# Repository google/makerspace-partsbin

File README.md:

# Makerspace Partsbin

This repository houses various things (3D models, circuits, class materials)
that we've created for use in Google makerspaces.

If you'd like to contribute, see [CONTRIBUTING](CONTRIBUTING.md)

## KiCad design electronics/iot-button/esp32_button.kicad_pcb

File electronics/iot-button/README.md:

# IoT Button

This is a single-button (with some IOs broken out) that can use deep sleep or
fully turn off in between uses.

Stack-up, inside a 3d printed case...

    Button Cap
    Board (0.8mm)
    Small LiPO

Results in a pretty small overall package that's not quite pocket-sized.

## Build

The build by hand will probably require a microscope (for Q301, part of the
auto-reset circuit) and a very good soldering iron (exposed pads, although there
vias so you can head from the other side).

The USB connector is one that doesn't require slots for mounting, so this board
can be made at osh park.

## Verification

The power-off functionality works, on wakeup you need to assert IO12 as long as
you want to stay powered-up.  The U402 (single pixel) works, although it draws a
*lot* from the 3v3 rail.  The IO4 voltage measurement is expected to only work
as a rough measurement, given results on previous similar circuits.

## USB Power

The overall power budget is an estimate that hasn't been verified yet.  Maximum
stable draw is with an exhausted LiPO + busy ESP32, and the draw at the USB
port shouldn't exceed 500mA.

Capacitance has been minimized that would affect inrush current, and previous
prototypes with similar circuits were acceptable, but this should be measured.

## Known Issues

* v0.3
  * some broken-out IOs are unusable
  * regulator part number is incorrect; it needs one with higher current
  * CH340 variant can't program faster than 115k (perhaps a limitation of the
    xtal-less one)
* v0.2
  * url is wrong, U402 rotated 180

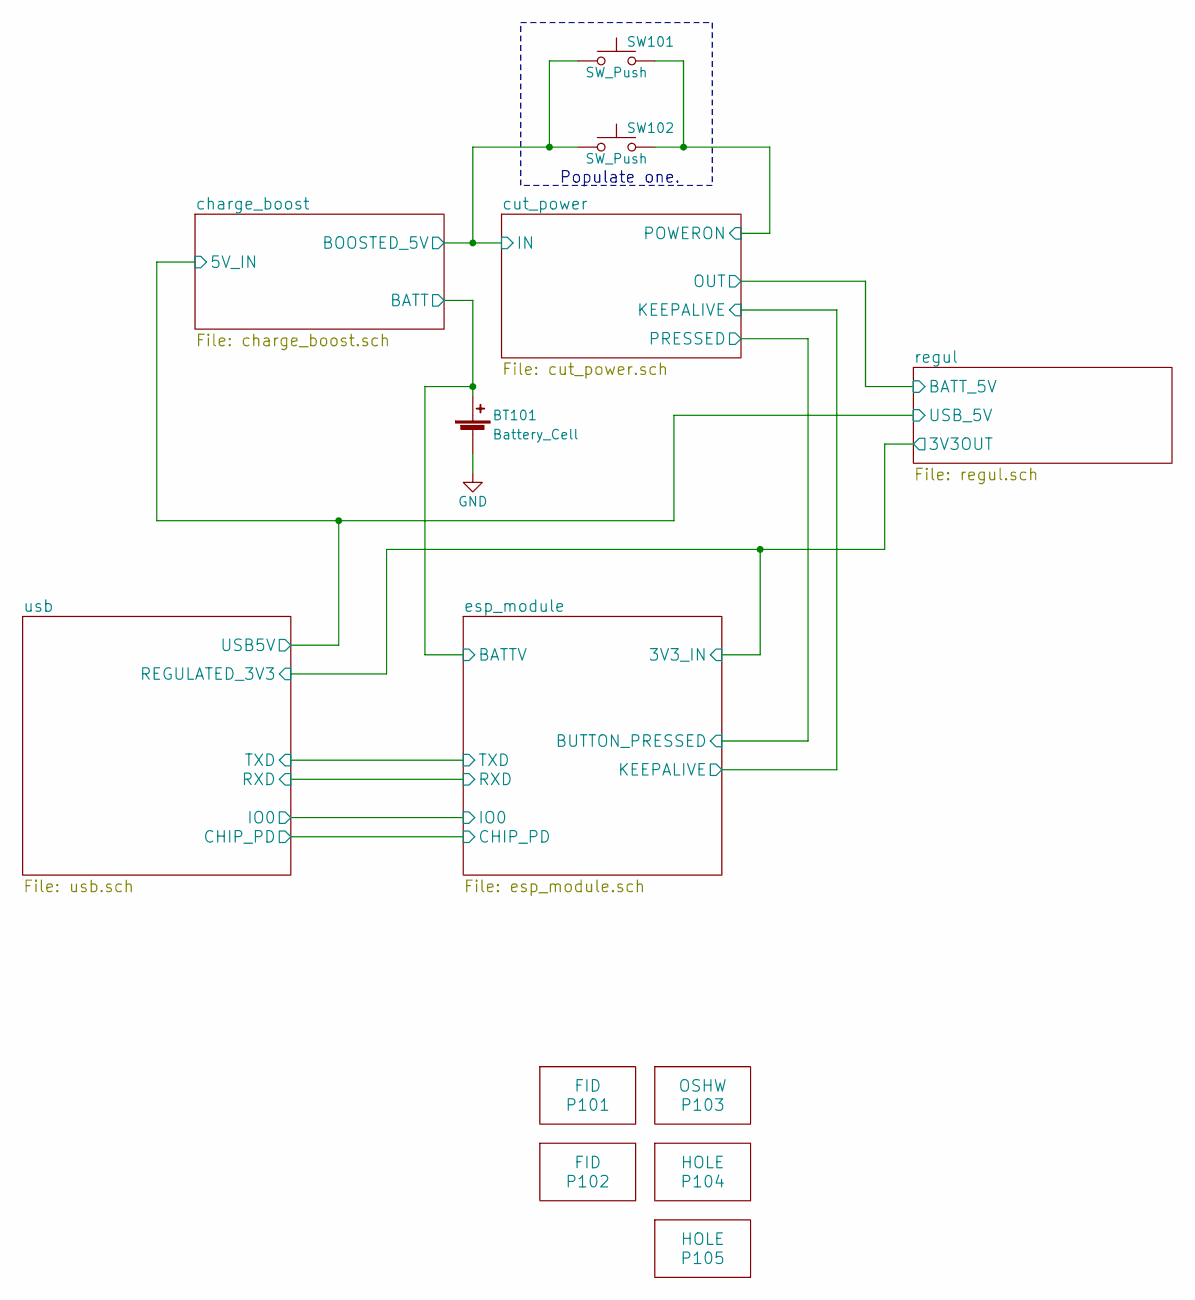
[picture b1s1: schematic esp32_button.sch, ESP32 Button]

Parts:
BT101: Battery_Cell; JST_PH_2_Combo; MPN S2B-PH-K-S(LF)(SN)
P101, P102: FID; Fiducial_1mm_Dia_2.54mm_Outer_CopperTop
P103: OSHW; OSHW-Symbol_8.9x8mm_SilkScreen
P104, P105: HOLE; MountingHole_3mm
SW101: SW_Push; SW_SPST_EVQP0
SW102: SW_Push; SW_SPST_PTS645; MPN? PTS525SM15SMTR2 LFS

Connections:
/charge_boost/BATT: BT101.1 (+); also elsewhere on the board
/charge_boost/BOOSTED_5V: SW101.1, SW102.1; also elsewhere on the board
/cut_power/POWERON: SW101.2, SW102.2; also elsewhere on the board
GND: BT101.2 (-); also elsewhere on the board

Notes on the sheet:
Populate one.

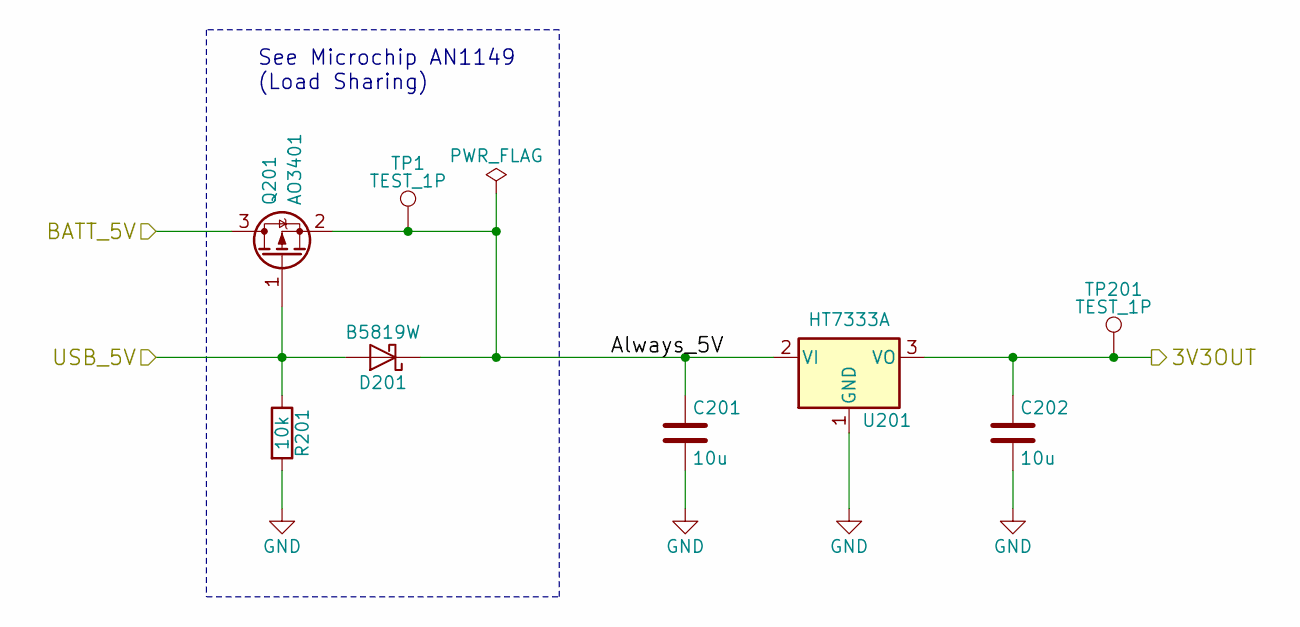
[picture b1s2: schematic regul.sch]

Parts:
C201, C202: 10u; C_0805
D201: B5819W; D_SOD-123; MPN B5819WS-TP
Q201: AO3401; SOT-23
R201: 10k; R_0603_HandSoldering
TP1, TP201: TEST_1P; Test_Point_SMD
U201: HT7333A; SOT-89-3

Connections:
/charge_boost/5V_IN: D201.2 (A), Q201.1 (G), R201.1; also elsewhere on the board
/regul/3V3OUT: C202.1, TP201.1, U201.3 (VO); also elsewhere on the board
/regul/Always_5V: C201.1, D201.1 (K), Q201.2 (S), TP1.1, U201.2 (VI)
/regul/BATT_5V: Q201.3 (D); also elsewhere on the board
GND: C201.2, C202.2, R201.2, U201.1 (GND); also elsewhere on the board

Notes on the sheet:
See Microchip AN1149 (Load Sharing)

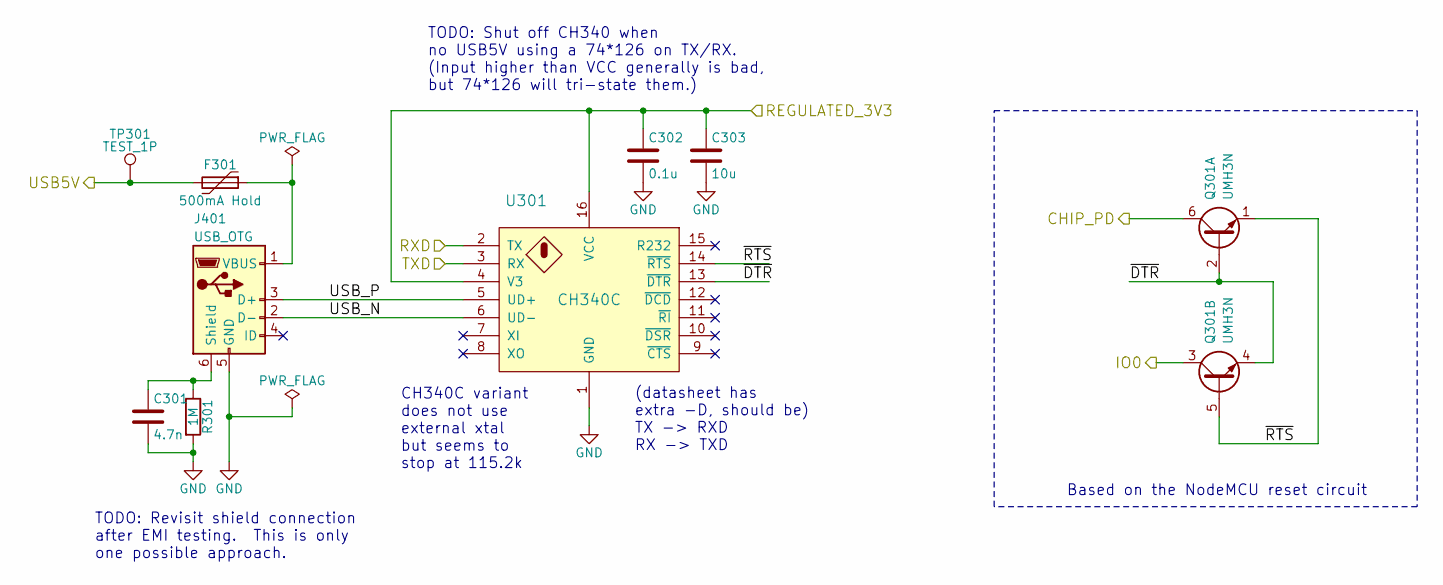
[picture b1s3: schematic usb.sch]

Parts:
C301: 4.7n; C_0603; MPN GRM188R71H472KA01D
C302: 0.1u; C_0603
C303: 10u; C_0805; MPN C0805C106K8PACTU
F301: 500mA Hold; Fuse_SMD1206_HandSoldering; MPN 0ZCJ0050FF2G
J401: USB_OTG; USB_Micro-B_Amphenol-10118194-0001LF_CircularHoles; MPN 10118194-0001LF
Q301: UMH3N; SOT-363_SC-70-6_Handsoldering
R301: 1M; R_0603_HandSoldering
TP301: TEST_1P; Test_Point_SMD
U401: CH340C; SOIC-16_3.9x9.9mm_Pitch1.27mm

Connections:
/charge_boost/5V_IN: F301.2, TP301.1; also elsewhere on the board
/esp_module/CHIP_PD: Q301.6 (C1); also elsewhere on the board
/esp_module/IO0: Q301.3 (C2); also elsewhere on the board
/regul/3V3OUT: C302.1, C303.1; also elsewhere on the board
/usb/USB_N: J401.2 (D-); also elsewhere on the board
/usb/USB_P: J401.3 (D+); also elsewhere on the board
/usb/~DTR: Q301.2 (B1), Q301.4 (E2); also elsewhere on the board
/usb/~RTS: Q301.1 (E1), Q301.5 (B2); also elsewhere on the board
GND: C301.2, C302.2, C303.2, J401.5 (GND), R301.2; also elsewhere on the board
unnamed: C301.1, J401.6 (Shield), R301.1
unnamed: F301.1, J401.1 (VBUS)

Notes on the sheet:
Based on the NodeMCU reset circuit
CH340C variant does not use external xtal but seems to stop at 115.2k
TODO: Shut off CH340 when no USB5V using a 74*126 on TX/RX. (Input higher than VCC generally is bad, but 74*126 will tri-state them.)
TODO: Revisit shield connection after EMI testing. This is only one possible approach.
(datasheet has extra -D, should be) TX -> RXD RX -> TXD

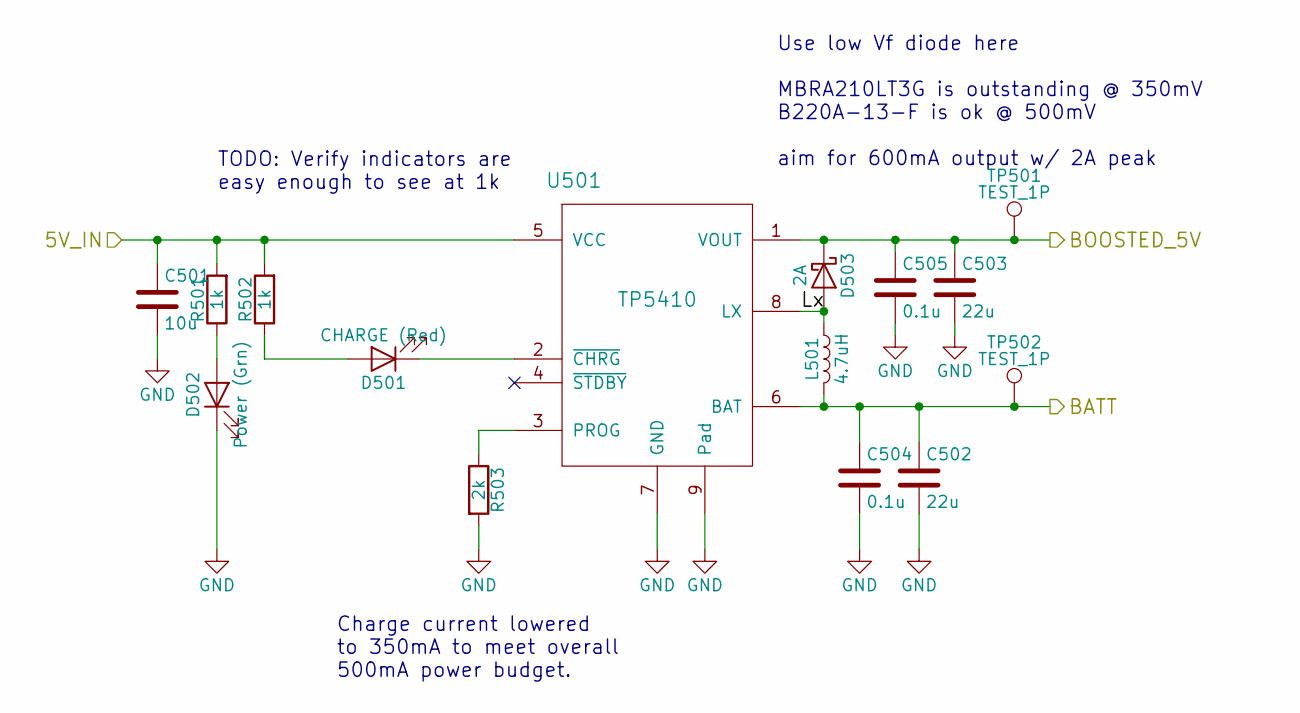
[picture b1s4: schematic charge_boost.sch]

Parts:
C501: 10u; C_0805
C502, C503: 22u; C_0805; MPN C0805C226M8PAC7800
C504: 0.1u; C_0603
C505: 0.1u; C_0603; MPN GRM033R61A104KE15D
D501: CHARGE (Red); LED_0603; MPN SML-D12V8WT86
D502: Power (Grn); LED_0603; MPN SML-D13M8WT86
D503: 2A; D_SMB; MPN MBRA210LT3G
L501: 4.7uH; Inductor_Taiyo-Yuden_NR-40xx_HandSoldering; MPN ASPI-4030S-4R7M-T
R501, R502: 1k; R_0402
R503: 2k; R_0603_HandSoldering
TP501, TP502: TEST_1P; Test_Point_SMD
U501: TP5410; SOIC-8-1EP_3.9x4.9mm_Pitch1.27mm

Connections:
/charge_boost/5V_IN: C501.1, R501.2, R502.2, U501.5 (VCC); also elsewhere on the board
/charge_boost/BATT: C502.1, C504.1, L501.2, TP502.1, U501.6 (BAT); also elsewhere on the board
/charge_boost/BOOSTED_5V: C503.1, C505.1, D503.1 (K), TP501.1, U501.1 (VOUT); also elsewhere on the board
/charge_boost/Lx: D503.2 (A), L501.1, U501.8 (LX)
GND: C501.2, C502.2, C503.2, C504.2, C505.2, D502.1 (K), R503.2, U501.7 (GND), U501.9 (Pad); also elsewhere on the board
unnamed: D501.1 (K), U501.2 (~CHRG)
unnamed: D501.2 (A), R502.1
unnamed: D502.2 (A), R501.1
unnamed: R503.1, U501.3 (PROG)

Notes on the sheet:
Charge current lowered to 350mA to meet overall 500mA power budget.
Use low Vf diode here MBRA210LT3G is outstanding @ 350mV B220A-13-F is ok @ 500mV aim for 600mA output w/ 2A peak
TODO: Verify indicators are easy enough to see at 1k

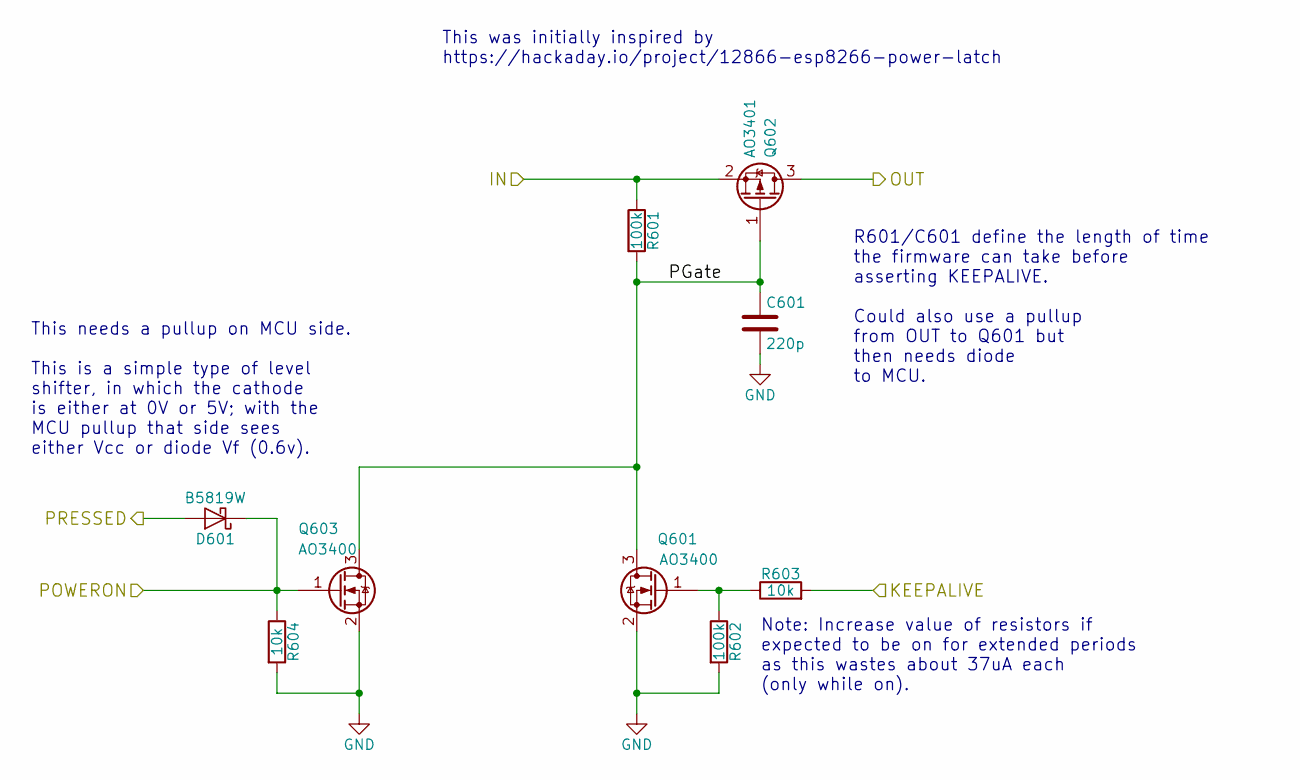
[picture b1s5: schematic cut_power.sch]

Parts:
C601: 220p; C_0603; MPN C1608X7R1C224K080AC
D601: B5819W; D_SOD-123; MPN B5819WS-TP
Q601, Q603: AO3400; SOT-23
Q602: AO3401; SOT-23
R601, R602: 100k; R_0603_HandSoldering
R603, R604: 10k; R_0603_HandSoldering

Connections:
/charge_boost/BOOSTED_5V: Q602.2 (S), R601.1; also elsewhere on the board
/cut_power/KEEPALIVE: R603.2; also elsewhere on the board
/cut_power/PGate: C601.1, Q601.3 (D), Q602.1 (G), Q603.3 (D), R601.2
/cut_power/POWERON: D601.1 (K), Q603.1 (G), R604.1; also elsewhere on the board
/esp_module/BUTTON_PRESSED: D601.2 (A); also elsewhere on the board
/regul/BATT_5V: Q602.3 (D); also elsewhere on the board
GND: C601.2, Q601.2 (S), Q603.2 (S), R602.2, R604.2; also elsewhere on the board
unnamed: Q601.1 (G), R602.1, R603.1

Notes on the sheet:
Note: Increase value of resistors if expected to be on for extended periods as this wastes about 37uA each (only while on).
R601/C601 define the length of time the firmware can take before asserting KEEPALIVE. Could also use a pullup from OUT to Q601 but then needs diode to MCU.
This was initially inspired by https://hackaday.io/project/12866-esp8266-power-latch
This needs a pullup on MCU side. This is a simple type of level shifter, in which the cathode is either at 0V or 5V; with the MCU pullup that side sees either Vcc or diode Vf (0.6v).

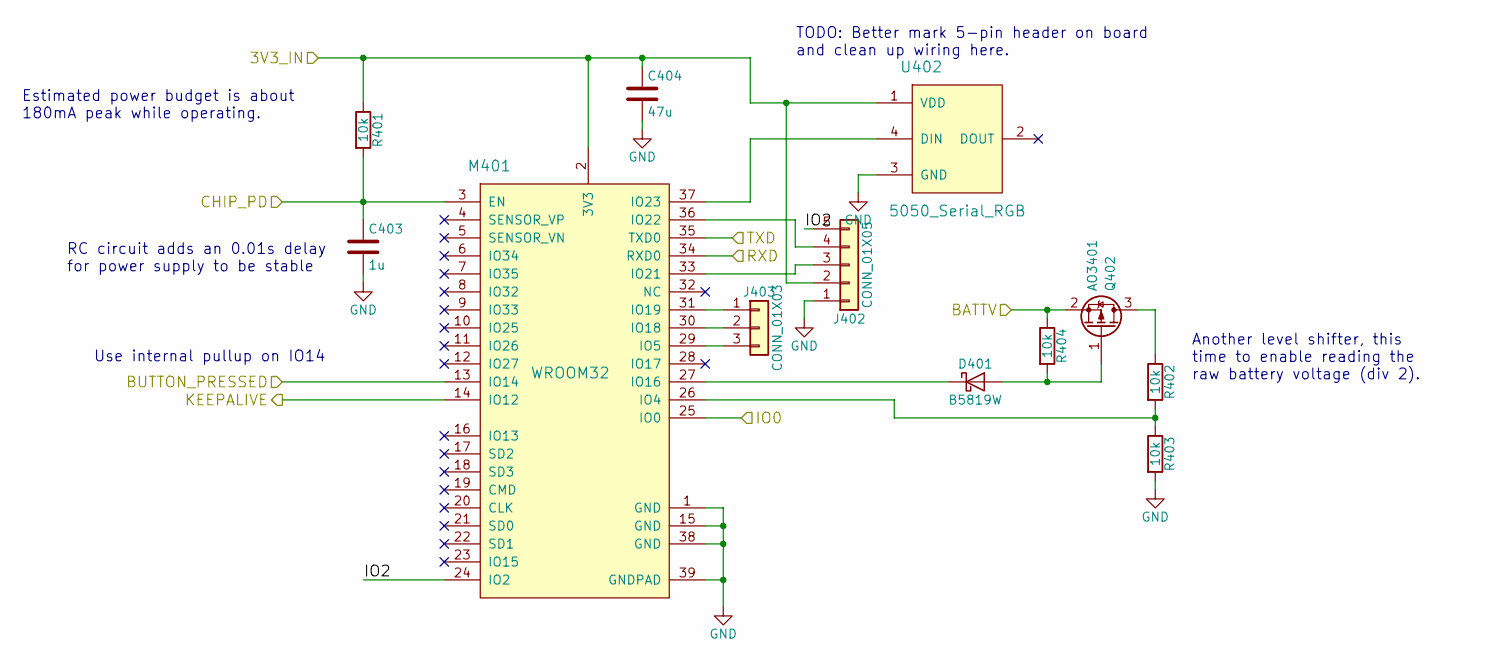
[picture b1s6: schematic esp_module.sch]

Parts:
C403: 1u; C_0805; MPN C0805C105K3PACTU
C404: 47u; C_1206; MPN C1206C476M9PACTU
D401: B5819W; D_SOD-123; MPN B5819WS-TP
J402: CONN_01X05; Pin_Header_Straight_1x05_Pitch2.54mm
J403: CONN_01X03; Pin_Header_Straight_1x03_Pitch2.54mm
M401: WROOM32
Q402: AO3401; SOT-23
R401, R402, R403, R404: 10k; R_0603_HandSoldering
U402: 5050_Serial_RGB; LED_WS2812B-PLCC4

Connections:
/charge_boost/BATT: Q402.2 (S), R404.1; also elsewhere on the board
/cut_power/KEEPALIVE: M401.14 (IO12); also elsewhere on the board
/esp_module/BUTTON_PRESSED: M401.13 (IO14); also elsewhere on the board
/esp_module/CHIP_PD: C403.1, M401.3 (EN), R401.2; also elsewhere on the board
/esp_module/IO0: M401.25 (IO0); also elsewhere on the board
/esp_module/IO2: J402.5, M401.24 (IO2)
/esp_module/RXD: M401.34 (RXD0); also elsewhere on the board
/esp_module/TXD: M401.35 (TXD0); also elsewhere on the board
/regul/3V3OUT: C404.1, J402.2, M401.2 (3V3), R401.1, U402.1 (VDD); also elsewhere on the board
GND: C403.2, C404.2, J402.1, M401.1 (GND), M401.15 (GND), M401.38 (GND), M401.39 (GNDPAD), R403.2, U402.3 (GND); also elsewhere on the board
unnamed: D401.1 (K), M401.27 (IO16)
unnamed: D401.2 (A), Q402.1 (G), R404.2
unnamed: J402.3, M401.33 (IO21)
unnamed: J402.4, M401.36 (IO22)
unnamed: J403.1, M401.31 (IO19)
unnamed: J403.2, M401.30 (IO18)
unnamed: J403.3, M401.29 (IO5)
unnamed: M401.26 (IO4), R402.2, R403.1
unnamed: M401.37 (IO23), U402.4 (DIN)
unnamed: Q402.3 (D), R402.1

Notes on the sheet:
TODO: Better mark 5-pin header on board and clean up wiring here.
RC circuit adds an 0.01s delay for power supply to be stable
Use internal pullup on IO14
Estimated power budget is about 180mA peak while operating.
Another level shifter, this time to enable reading the raw battery voltage (div 2).

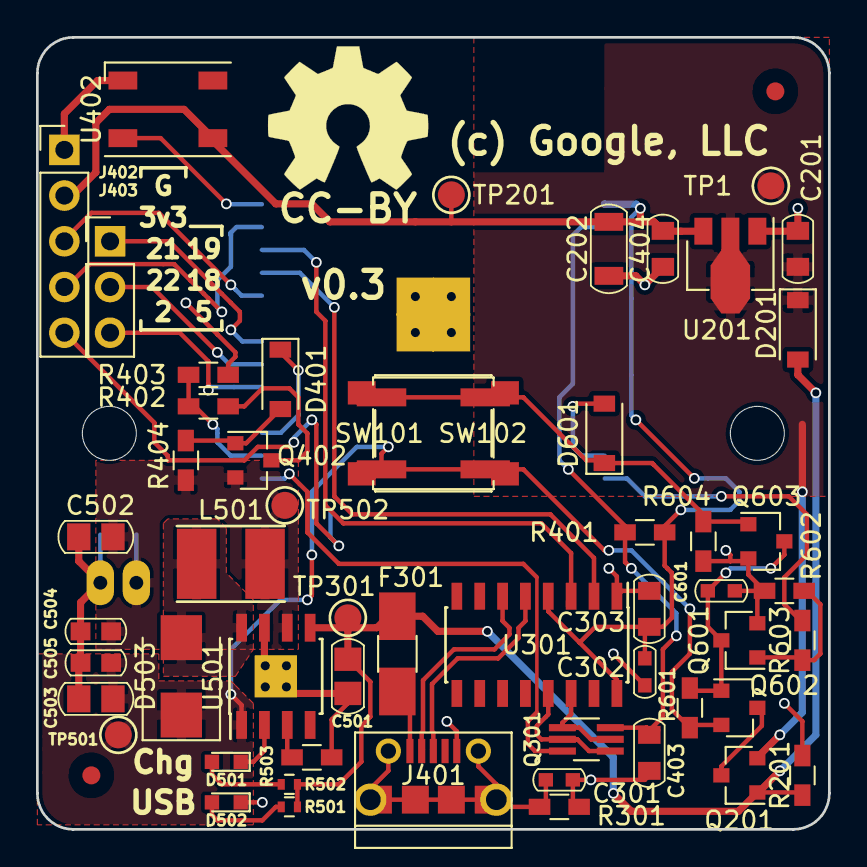
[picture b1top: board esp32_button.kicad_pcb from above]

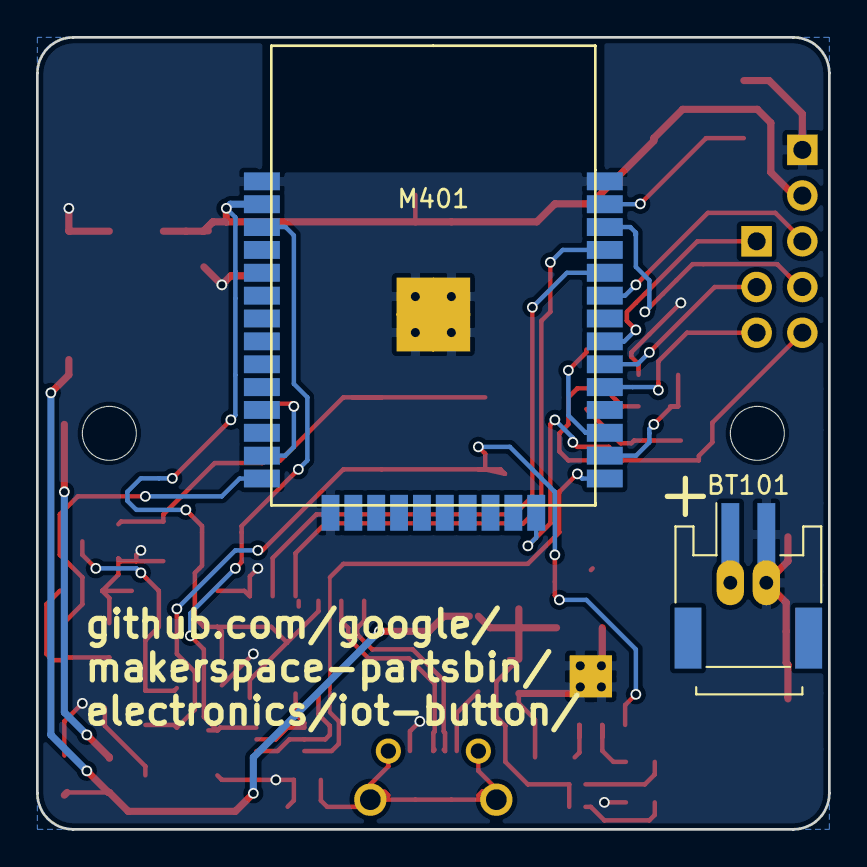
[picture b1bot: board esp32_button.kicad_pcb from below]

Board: 2 copper layers, 44.0 x 44.0 mm, 61 parts (2 on the bottom side), 38 nets.

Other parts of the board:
U301: CH340C; SOIC-16_3.9x9.9mm_Pitch1.27mm

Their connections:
/esp_module/RXD: U301.2; also elsewhere on the board
/esp_module/TXD: U301.3; also elsewhere on the board
/regul/3V3OUT: U301.4, U301.16; also elsewhere on the board
/usb/USB_N: U301.6; also elsewhere on the board
/usb/USB_P: U301.5; also elsewhere on the board
/usb/~DTR: U301.13; also elsewhere on the board
/usb/~RTS: U301.14; also elsewhere on the board
GND: U301.1; also elsewhere on the board

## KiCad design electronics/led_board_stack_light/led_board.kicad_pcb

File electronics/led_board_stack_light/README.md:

This is a work-in-progress to build a laser-cuttable stack light.  Best if the
soldermask is white.

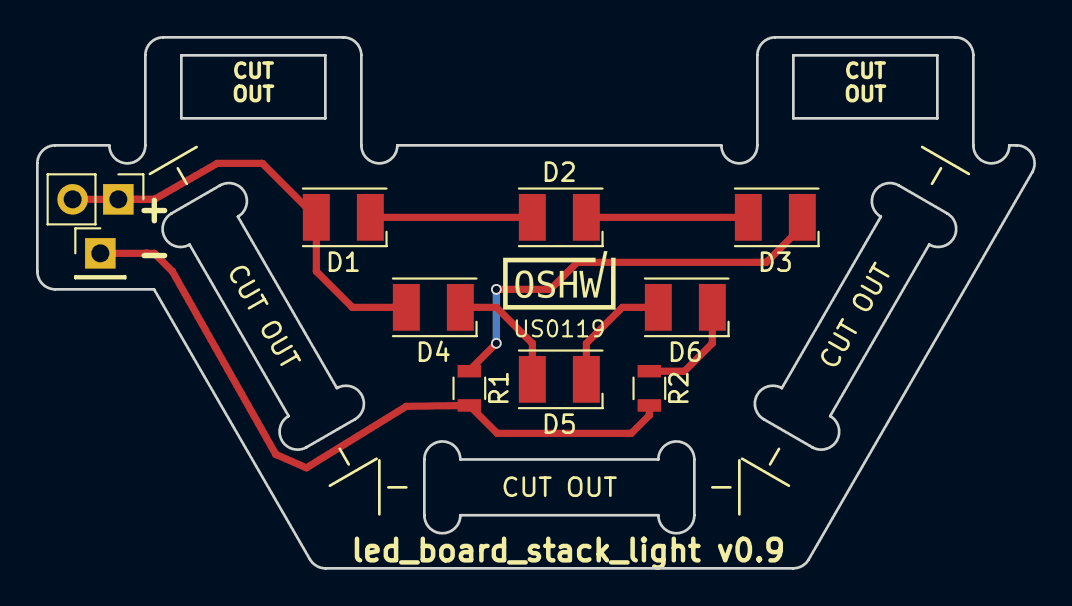
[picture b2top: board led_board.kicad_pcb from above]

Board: 2 copper layers, 55.4 x 29.5 mm, 15 parts (1 on the bottom side), 8 nets.

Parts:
D1, D2, D3, D4, D5, D6: LED; LED_PLCC-2
J1: CONN_01X02; Pin_Header_Straight_1x02_Pitch2.54mm
J2: CONN_01X01; Pin_Header_Straight_1x01_Pitch2.54mm
P1: OSHW; OSHW-Logo2_9.8x8mm_SilkScreen
P2, P3, P4: Slot; Slot_3.1x15
P5: US0119; OSHW_Mono_0.15_Scale
R1, R2: 56R; R_0805

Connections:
unnamed: D1.1, D2.2
unnamed: D1.2, D4.2, J1.1, J1.2
unnamed: D2.1, D3.2
unnamed: D3.1, R1.1
unnamed: D4.1, D5.2
unnamed: D5.1, D6.2
unnamed: D6.1, R2.1
unnamed: J2.1, R1.2, R2.2

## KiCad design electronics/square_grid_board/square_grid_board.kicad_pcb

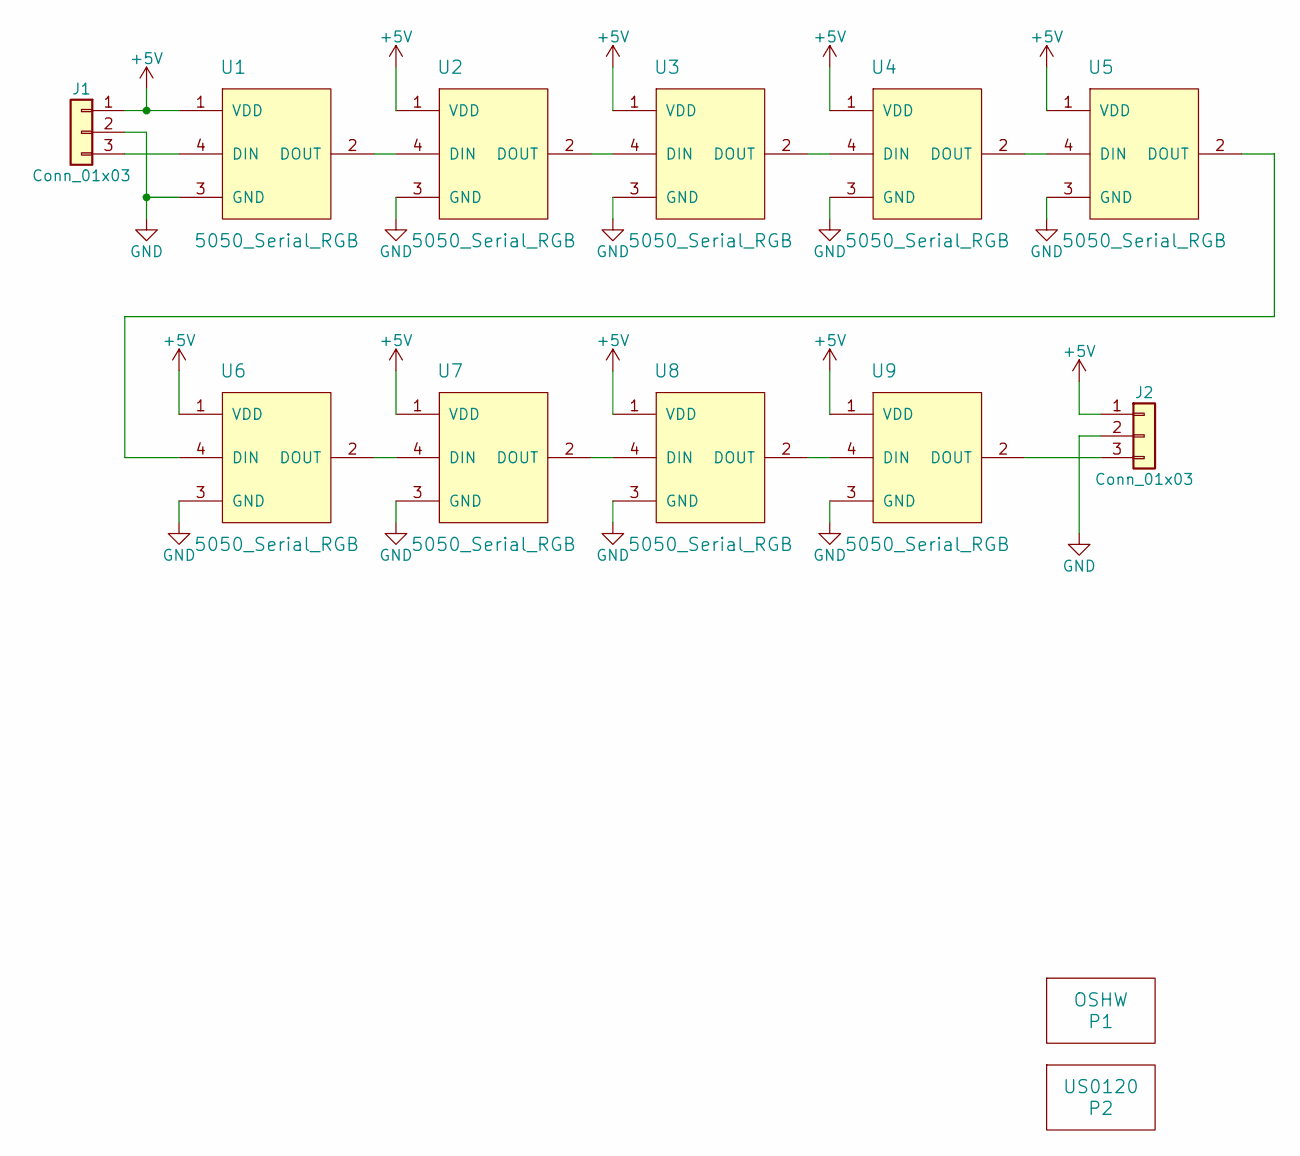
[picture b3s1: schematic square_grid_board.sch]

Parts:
J1, J2: Conn_01x03; JST_XH_S03B-XH-A_03x2.50mm_Angled
P1: OSHW; OSHW-Logo2_7.3x6mm_SilkScreen
P2: US0120; OSHW_Mono_0.20_Scale
U1, U2, U3, U4, U5, U6, U7, U8, U9: 5050_Serial_RGB; LED_WS2812B-PLCC4

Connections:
+5V: J1.1, J2.1, U1.1 (VDD), U2.1 (VDD), U3.1 (VDD), U4.1 (VDD), U5.1 (VDD), U6.1 (VDD), U7.1 (VDD), U8.1 (VDD), U9.1 (VDD)
GND: J1.2, J2.2, U1.3 (GND), U2.3 (GND), U3.3 (GND), U4.3 (GND), U5.3 (GND), U6.3 (GND), U7.3 (GND), U8.3 (GND), U9.3 (GND)
unnamed: J1.3, U1.4 (DIN)
unnamed: J2.3, U9.2 (DOUT)
unnamed: U1.2 (DOUT), U2.4 (DIN)
unnamed: U2.2 (DOUT), U3.4 (DIN)
unnamed: U3.2 (DOUT), U4.4 (DIN)
unnamed: U4.2 (DOUT), U5.4 (DIN)
unnamed: U5.2 (DOUT), U6.4 (DIN)
unnamed: U6.2 (DOUT), U7.4 (DIN)
unnamed: U7.2 (DOUT), U8.4 (DIN)
unnamed: U8.2 (DOUT), U9.4 (DIN)

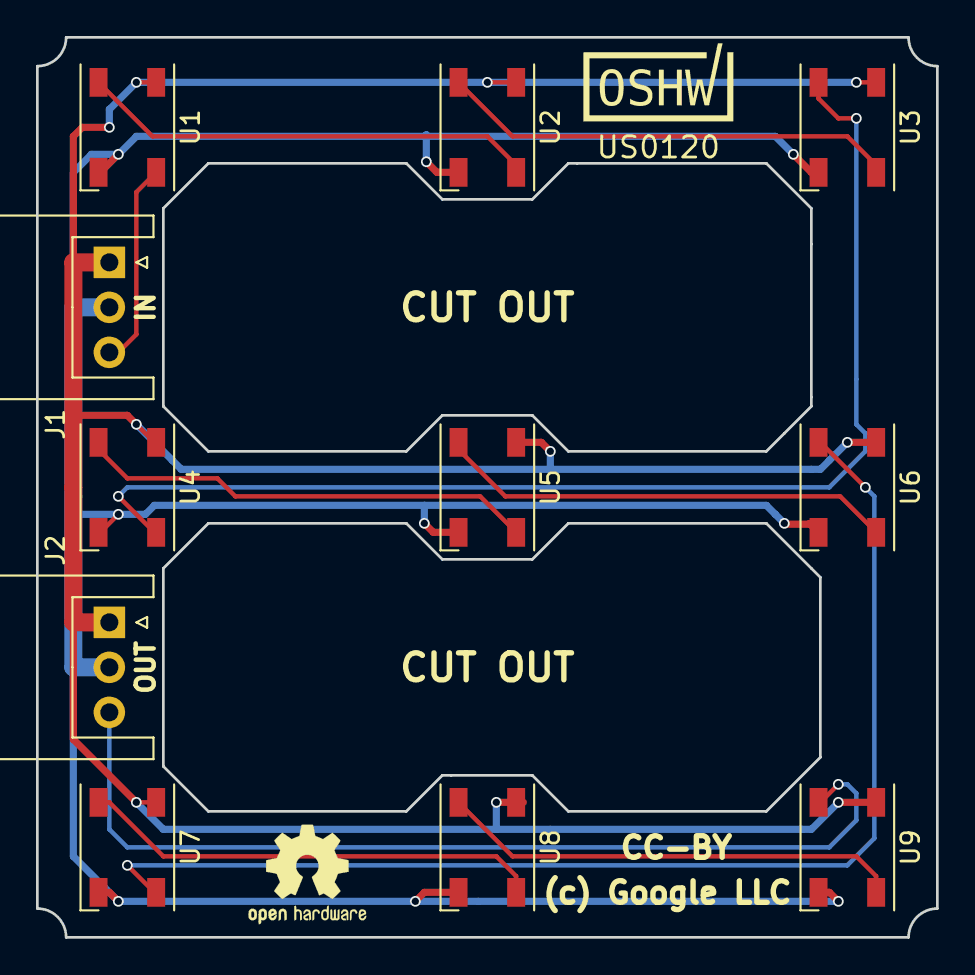
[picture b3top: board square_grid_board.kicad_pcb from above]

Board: 2 copper layers, 50.0 x 50.0 mm, 13 parts (0 on the bottom side), 12 nets.

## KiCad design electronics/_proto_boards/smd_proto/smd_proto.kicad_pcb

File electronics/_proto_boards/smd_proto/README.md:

This board is inspired by https://www.sparkfun.com/products/retired/8708 , https://hackaday.io/project/852-makermod-system/log/6386-first-prototypes , and https://blog.adafruit.com/2013/05/14/63597/

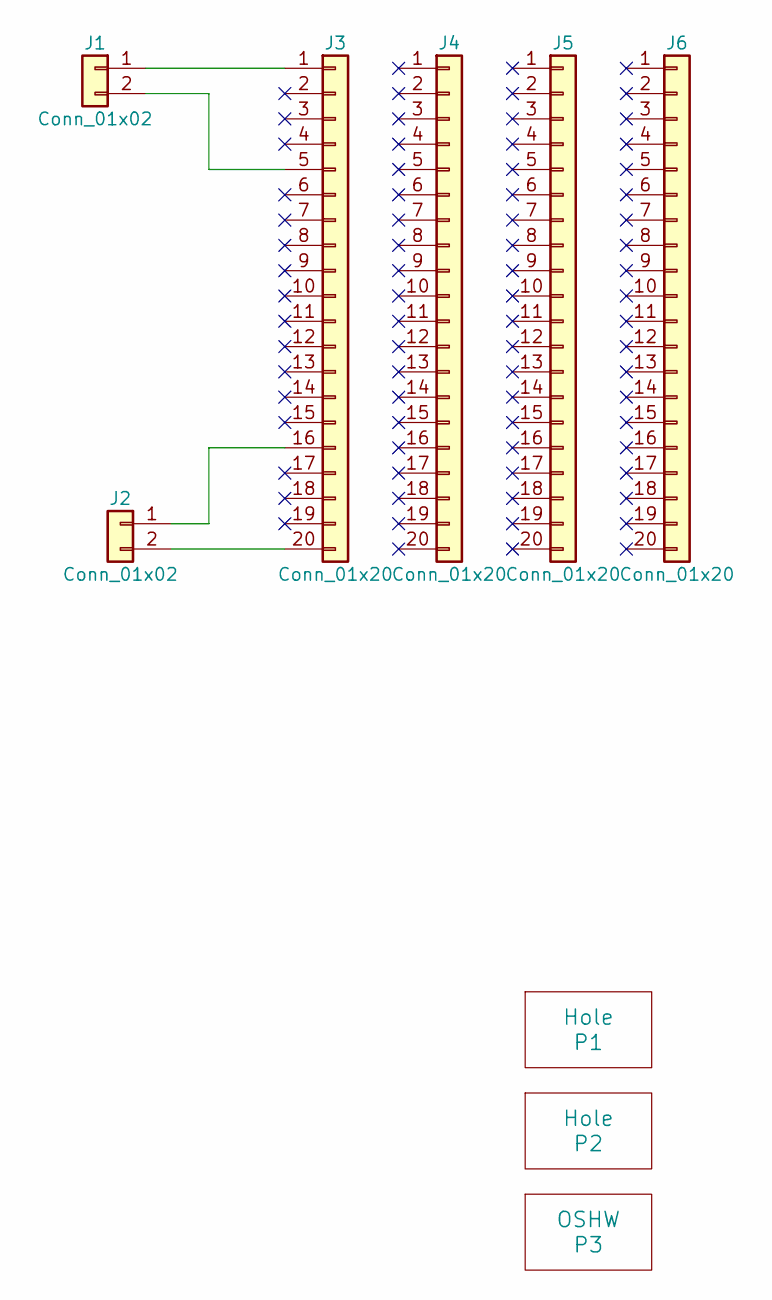
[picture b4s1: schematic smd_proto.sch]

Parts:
J1, J2: Conn_01x02; Pin_Header_Straight_1x02_Pitch2.54mm
J3: Conn_01x20; Strip_20
J4, J5, J6: Conn_01x20; Strip_20x10_NC
P1, P2: Hole; MountingHole_3.2mm_M3_DIN965
P3: OSHW; OSHW-Logo2_7.3x6mm_SilkScreen

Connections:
unnamed: J1.1, J3.1
unnamed: J1.2, J3.5
unnamed: J2.1, J3.16
unnamed: J2.2, J3.20

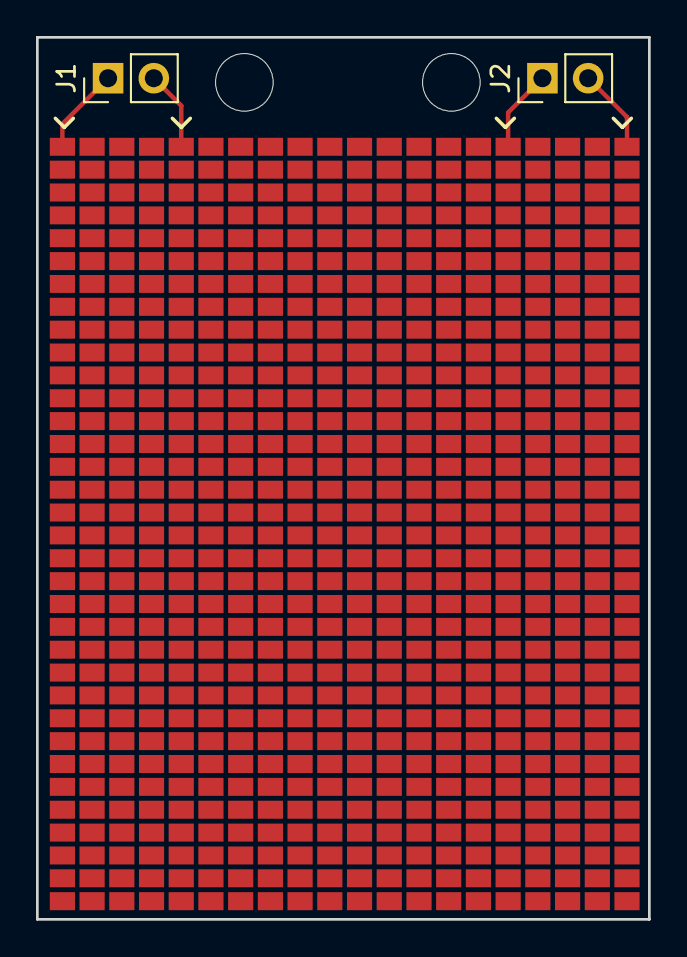
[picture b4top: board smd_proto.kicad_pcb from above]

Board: 2 copper layers, 34.0 x 49.0 mm, 9 parts (1 on the bottom side), 4 nets.

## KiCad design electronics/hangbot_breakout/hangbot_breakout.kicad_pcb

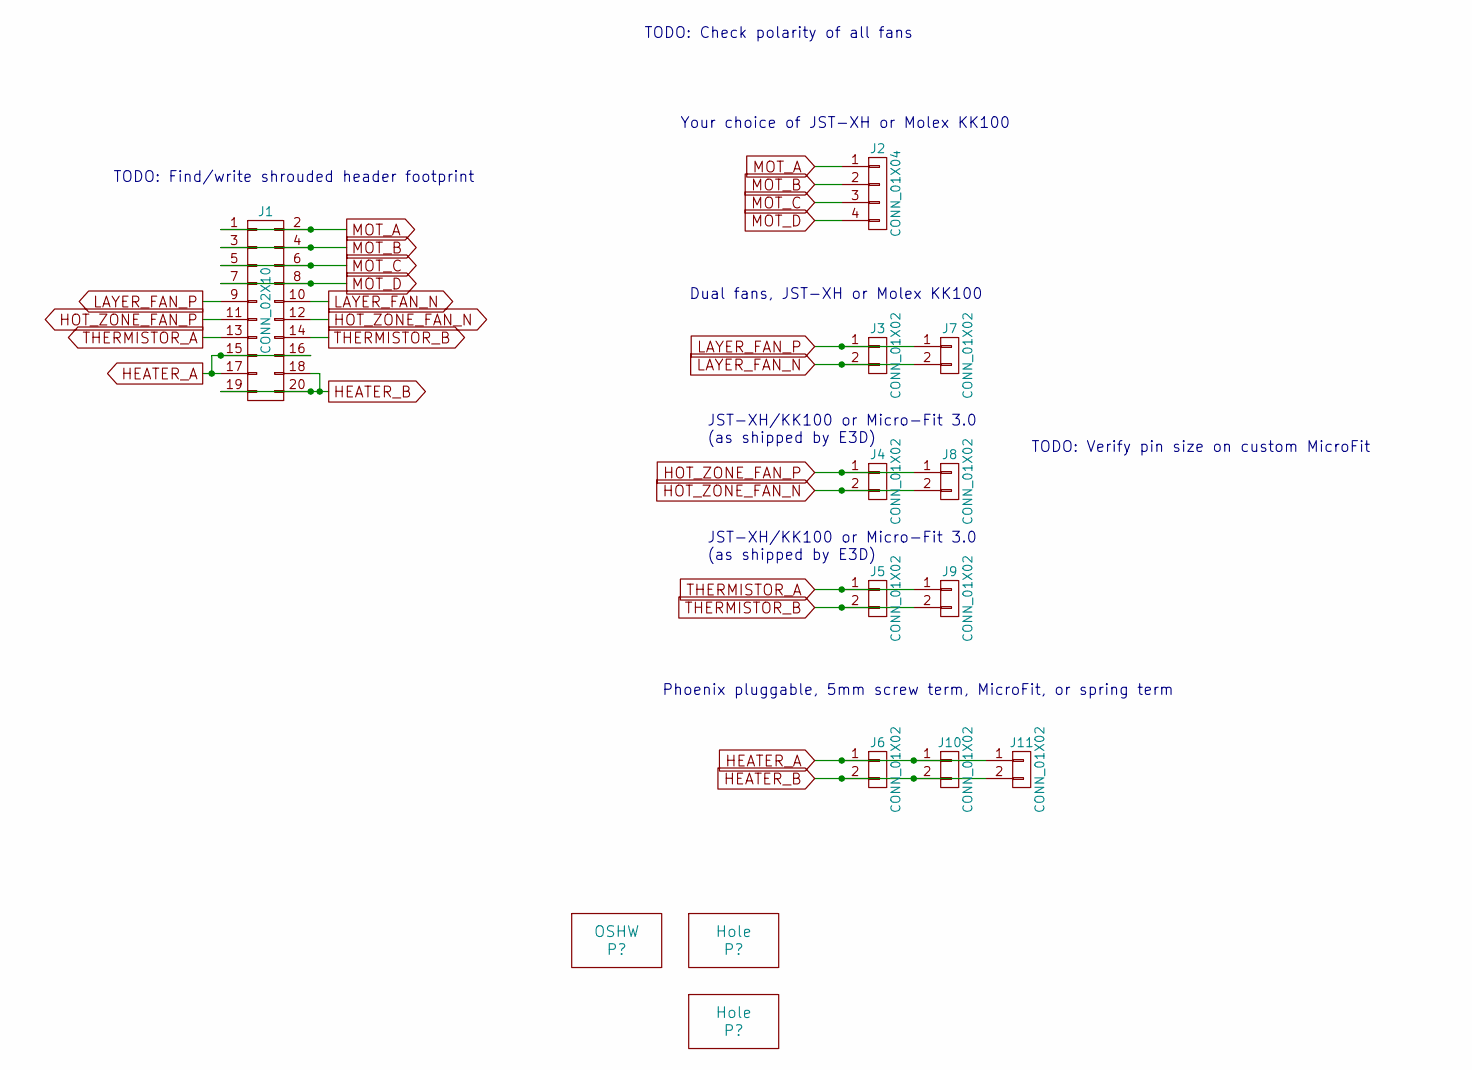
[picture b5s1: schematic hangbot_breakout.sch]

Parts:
J1: CONN_02X10; Multicomp_MC9A12-2034_2x10x2.54mm_Straight
J2: CONN_01X04; Molex_KK-6410-04_04x2.54mm_Straight
J3, J4, J5, J7: CONN_01X02; Molex_KK-6410-02_02x2.54mm_Straight
J6: CONN_01X02; PhoenixContact_MSTBA-G_02x5.08mm_Angled
J8, J9, J10: CONN_01X02; Molex_MicroFit_43650-0200_2Pin
J11: CONN_01X02; KF235_2Pin_3.81mm

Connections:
HEATER_A: J1.15, J1.16, J1.17, J6.1, J10.1, J11.1
HEATER_B: J1.18, J1.19, J1.20, J6.2, J10.2, J11.2
HOT_ZONE_FAN_N: J1.12, J4.2, J8.2
HOT_ZONE_FAN_P: J1.11, J4.1, J8.1
LAYER_FAN_N: J1.10, J3.2, J7.2
LAYER_FAN_P: J1.9, J3.1, J7.1
MOT_A: J1.1, J1.2, J2.1
MOT_B: J1.3, J1.4, J2.2
MOT_C: J1.5, J1.6, J2.3
MOT_D: J1.7, J1.8, J2.4
THERMISTOR_A: J1.13, J5.1, J9.1
THERMISTOR_B: J1.14, J5.2, J9.2

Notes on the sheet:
TODO: Find/write shrouded header footprint
Your choice of JST-XH or Molex KK100
Dual fans, JST-XH or Molex KK100
JST-XH/KK100 or Micro-Fit 3.0 (as shipped by E3D)
TODO: Check polarity of all fans
TODO: Verify pin size on custom MicroFit
Phoenix pluggable, 5mm screw term, MicroFit, or spring term

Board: 2 copper layers, 14 parts (0 on the bottom side), 12 nets, no tracks yet.

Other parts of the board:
P1: OSHW; OSHW-Logo2_9.8x8mm_SilkScreen
P2, P3: Hole; MountingHole_3.2mm_M3_Pad_Via

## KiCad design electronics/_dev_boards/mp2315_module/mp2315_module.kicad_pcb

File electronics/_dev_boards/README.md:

# Dev Boards

## ER-TFT024-3_breakout/

## mcp73831_breakout/

## mp2359_breakout/

## sot_23_5_breakout/

## sx1308_breakout/

## tp5410_breakout/

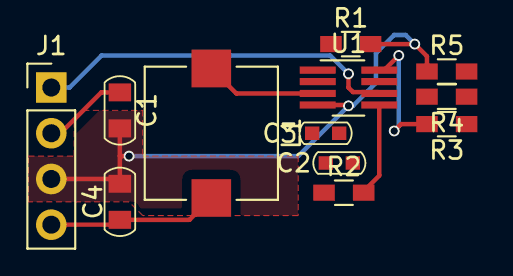
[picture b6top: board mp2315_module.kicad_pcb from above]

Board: 2 copper layers, 12 parts (0 on the bottom side), 11 nets.

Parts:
C1, C4: C; C_0805
C2, C3: C; C_0603
J1: CONN_01X04; Pin_Header_Straight_1x04_Pitch2.54mm
L1: L; L_7.3x7.3_Handsoldering
R1, R2, R3, R4, R5: R; R_0603_HandSoldering
U1: MP2315; TSOT-23-8_HandSoldering

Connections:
+12V: C1.1, J1.2, U1.2
/EN: J1.1, U1.6
/VOUT: C4.1, J1.4, L1.2, R4.2
GND: C1.2, C2.2, C4.2, J1.3, R1.2, R5.1, U1.4
unnamed: C2.1, U1.7
unnamed: C3.1, R2.1
unnamed: C3.2, L1.1, U1.3
unnamed: R1.1, U1.1
unnamed: R2.2, U1.5
unnamed: R3.1, R4.1, R5.2
unnamed: R3.2, U1.8

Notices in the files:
electronics/iot-button/charge_boost.sch:
(c) 2017-2019 Google
CC-BY 4.0 International
electronics/iot-button/esp32_button.kicad_pcb:
CC-BY
